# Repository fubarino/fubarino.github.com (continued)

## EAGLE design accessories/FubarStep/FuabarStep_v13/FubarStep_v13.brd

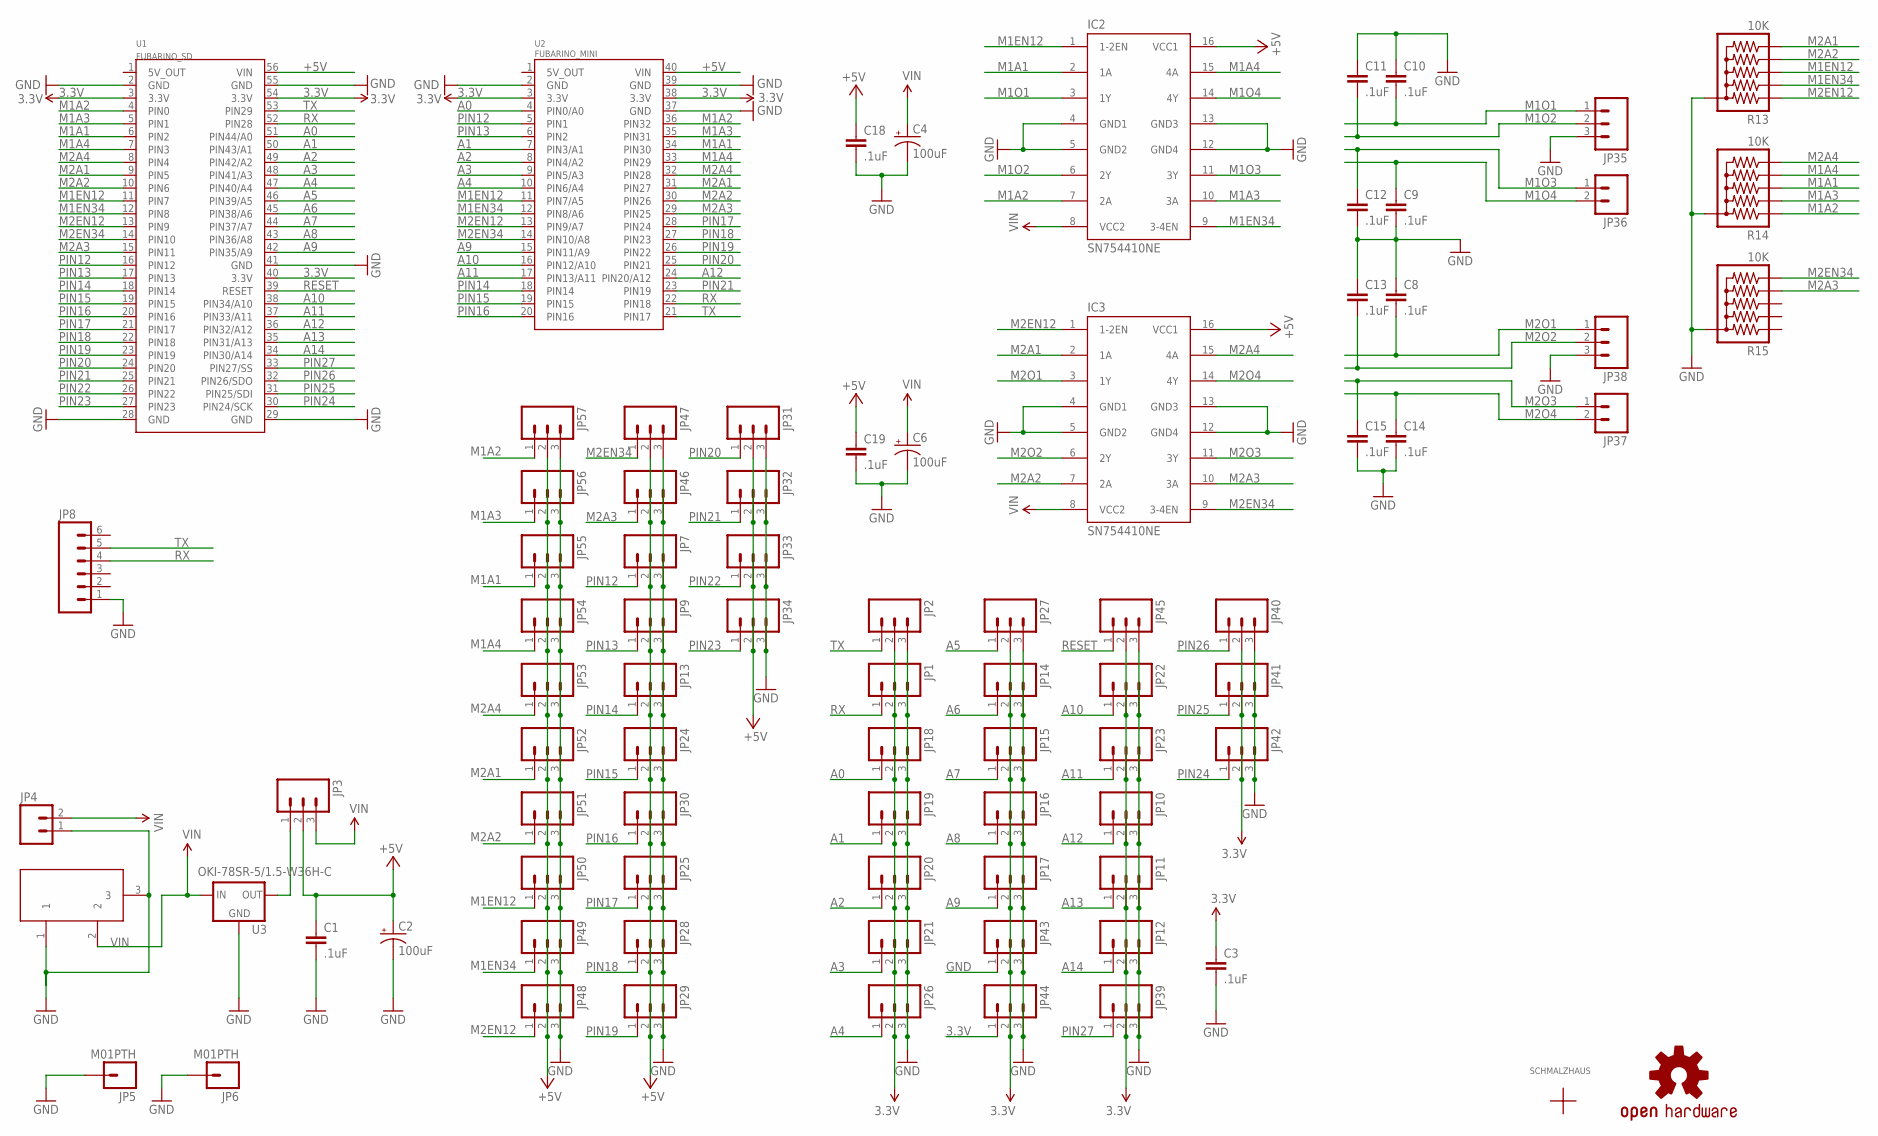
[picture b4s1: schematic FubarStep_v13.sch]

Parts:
C1, C3, C8, C9, C10, C11, C12, C13, C14, C15, C18, C19: .1uF; CAP-PTH-SMALL
C2, C4, C6: 100uF; CPOL-RADIAL-100UF
IC2, IC3: SN754410NE; DIL16
JP1, JP2, JP3, JP7, JP9, JP10, JP11, JP12, JP13, JP14, JP15, JP16, JP17, JP18, JP19, JP20, JP21, JP22, JP23, JP24, JP25, JP26, JP27, JP28, JP29, JP30, JP31, JP32, JP33, JP34, JP39, JP40, JP41, JP42, JP43, JP44, JP45, JP46, JP47, JP48, JP49, JP50, JP51, JP52, JP53, JP54, JP55, JP56, JP57: M03PTH; 1X03
JP4, JP36, JP37: M023.5MM; SCREWTERMINAL-3.5MM-2
JP5, JP6: M01PTH; 1X01
JP8: M06LOCK; 1X06_LOCK
JP35, JP38: M03SCREW; SCREWTERMINAL-3.5MM-3
LOGO1: OSHW-LOGOM; OSHW-LOGO-M
R13, R14, R15: 10K; RPACK-SIP-PTH-5
U1: FUBARINO_SD
U2: FUBARINO_MINI
U3: OKI-78SR-5/1.5-W36H-C; TO220-IGO
U$1: SCHMALZHAUSSCHMALZHAUS_SMALL; SCHMALZHAUS_SMALL
X1: DC21MMX; DC-21MM

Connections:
3.3V: C3.1, JP1.2, JP2.2, JP10.2, JP11.2, JP12.2, JP14.2, JP15.2, JP16.2, JP17.2, JP18.2, JP19.2, JP20.2, JP21.2, JP22.2, JP23.2, JP26.2, JP27.2, JP39.2, JP40.2, JP41.2, JP42.2, JP43.2, JP44.1, JP44.2, JP45.2, U1.3 (3.3V), U1.40 (3.3V), U1.54 (3.3V), U2.3 (3.3V), U2.38 (3.3V)
+5V: C1.1, C2.1 (+), C18.1, C19.1, IC2.16 (VCC1), IC3.16 (VCC1), JP3.2, JP7.2, JP9.2, JP13.2, JP24.2, JP25.2, JP28.2, JP29.2, JP30.2, JP31.2, JP32.2, JP33.2, JP34.2, JP46.2, JP47.2, JP48.2, JP49.2, JP50.2, JP51.2, JP52.2, JP53.2, JP54.2, JP55.2, JP56.2, JP57.2, U1.56 (VIN), U2.40 (VIN)
A0: JP18.1, U1.51 (PIN44/A0), U2.4 (PIN0/A0)
A1: JP19.1, U1.50 (PIN43/A1), U2.7 (PIN3/A1)
A2: JP20.1, U1.49 (PIN42/A2), U2.8 (PIN4/A2)
A3: JP21.1, U1.48 (PIN41/A3), U2.9 (PIN5/A3)
A4: JP26.1, U1.47 (PIN40/A4), U2.10 (PIN6/A4)
A5: JP27.1, U1.46 (PIN39/A5)
A6: JP14.1, U1.45 (PIN38/A6)
A7: JP15.1, U1.44 (PIN37/A7)
A8: JP16.1, U1.43 (PIN36/A8)
A9: JP17.1, U1.42 (PIN35/A9), U2.15 (PIN11/A9)
A10: JP22.1, U1.38 (PIN34/A10), U2.16 (PIN12/A10)
A11: JP23.1, U1.37 (PIN33/A11), U2.17 (PIN13/A11)
A12: JP10.1, U1.36 (PIN32/A12), U2.24 (PIN20/A12)
A13: JP11.1, U1.35 (PIN31/A13)
A14: JP12.1, U1.34 (PIN30/A14)
GND: C1.2, C2.2 (-), C3.2, C4.2 (-), C6.2 (-), C8.1, C9.2, C10.1, C11.1, C12.2, C13.1, C14.2, C15.2, C18.2, C19.2, IC2.4 (GND1), IC2.5 (GND2), IC2.12 (GND4), IC2.13 (GND3), IC3.4 (GND1), IC3.5 (GND2), IC3.12 (GND4), IC3.13 (GND3), JP1.3, JP2.3, JP4.1, JP5.1, JP6.1, JP7.3, JP8.1, JP9.3, JP10.3, JP11.3, JP12.3, JP13.3, JP14.3, JP15.3, JP16.3, JP17.3, JP18.3, JP19.3, JP20.3, JP21.3, JP22.3, JP23.3, JP24.3, JP25.3, JP26.3, JP27.3, JP28.3, JP29.3, JP30.3, JP31.3, JP32.3, JP33.3, JP34.3, JP35.3, JP38.3, JP39.3, JP40.3, JP41.3, JP42.3, JP43.1, JP43.3, JP44.3, JP45.3, JP46.3, JP47.3, JP48.3, JP49.3, JP50.3, JP51.3, JP52.3, JP53.3, JP54.3, JP55.3, JP56.3, JP57.3, R13.P$1 (1), R14.P$1 (1), R15.P$1 (1), U1.2 (GND), U1.28 (GND), U1.29 (GND), U1.41 (GND), U1.55 (GND), U2.2 (GND), U2.37 (GND), U2.39 (GND), U3.GND, X1.1, X1.3
M1A1: IC2.2 (1A), JP55.1, R14.P$4 (4), U1.6 (PIN2), U2.34 (PIN30)
M1A2: IC2.7 (2A), JP57.1, R14.P$2 (2), U1.4 (PIN0), U2.36 (PIN32)
M1A3: IC2.10 (3A), JP56.1, R14.P$3 (3), U1.5 (PIN1), U2.35 (PIN31)
M1A4: IC2.15 (4A), JP54.1, R14.P$5 (5), U1.7 (PIN3), U2.33 (PIN29)
M1EN12: IC2.1 (1-2EN), JP50.1, R13.P$4 (4), U1.11 (PIN7), U2.11 (PIN7/A5)
M1EN34: IC2.9 (3-4EN), JP49.1, R13.P$3 (3), U1.12 (PIN8), U2.12 (PIN8/A6)
M1O1: C10.2, IC2.3 (1Y), JP35.1
M1O2: C11.2, IC2.6 (2Y), JP35.2
M1O3: C12.1, IC2.11 (3Y), JP36.1
M1O4: C9.1, IC2.14 (4Y), JP36.2
M2A1: IC3.2 (1A), JP52.1, R13.P$6 (6), U1.9 (PIN5), U2.31 (PIN27)
M2A2: IC3.7 (2A), JP51.1, R13.P$5 (5), U1.10 (PIN6), U2.30 (PIN26)
M2A3: IC3.10 (3A), JP46.1, R15.P$5 (5), U1.15 (PIN11), U2.29 (PIN25)
M2A4: IC3.15 (4A), JP53.1, R14.P$6 (6), U1.8 (PIN4), U2.32 (PIN28)
M2EN12: IC3.1 (1-2EN), JP48.1, R13.P$2 (2), U1.13 (PIN9), U2.13 (PIN9/A7)
M2EN34: IC3.9 (3-4EN), JP47.1, R15.P$6 (6), U1.14 (PIN10), U2.14 (PIN10/A8)
M2O1: C8.2, IC3.3 (1Y), JP38.1
M2O2: C13.2, IC3.6 (2Y), JP38.2
M2O3: C15.1, IC3.11 (3Y), JP37.1
M2O4: C14.1, IC3.14 (4Y), JP37.2
unnamed: JP3.1, U3.OUT
PIN12: JP7.1, U1.16 (PIN12), U2.5 (PIN1)
PIN13: JP9.1, U1.17 (PIN13), U2.6 (PIN2)
PIN14: JP13.1, U1.18 (PIN14), U2.18 (PIN14)
PIN15: JP24.1, U1.19 (PIN15), U2.19 (PIN15)
PIN16: JP30.1, U1.20 (PIN16), U2.20 (PIN16)
PIN17: JP25.1, U1.21 (PIN17), U2.28 (PIN24)
PIN18: JP28.1, U1.22 (PIN18), U2.27 (PIN23)
PIN19: JP29.1, U1.23 (PIN19), U2.26 (PIN22)
PIN20: JP31.1, U1.24 (PIN20), U2.25 (PIN21)
PIN21: JP32.1, U1.25 (PIN21), U2.23 (PIN19)
PIN22: JP33.1, U1.26 (PIN22)
PIN23: JP34.1, U1.27 (PIN23)
PIN24: JP42.1, U1.30 (PIN24/SCK)
PIN25: JP41.1, U1.31 (PIN25/SDI)
PIN26: JP40.1, U1.32 (PIN26/SDO)
PIN27: JP39.1, U1.33 (PIN27/SS)
RESET: JP45.1, U1.39 (RESET)
RX: JP1.1, JP8.4, U1.52 (PIN28), U2.22 (PIN18)
TX: JP2.1, JP8.5, U1.53 (PIN29), U2.21 (PIN17)
VIN: C4.1 (+), C6.1 (+), IC2.8 (VCC2), IC3.8 (VCC2), JP3.3, JP4.2, U3.IN, X1.2

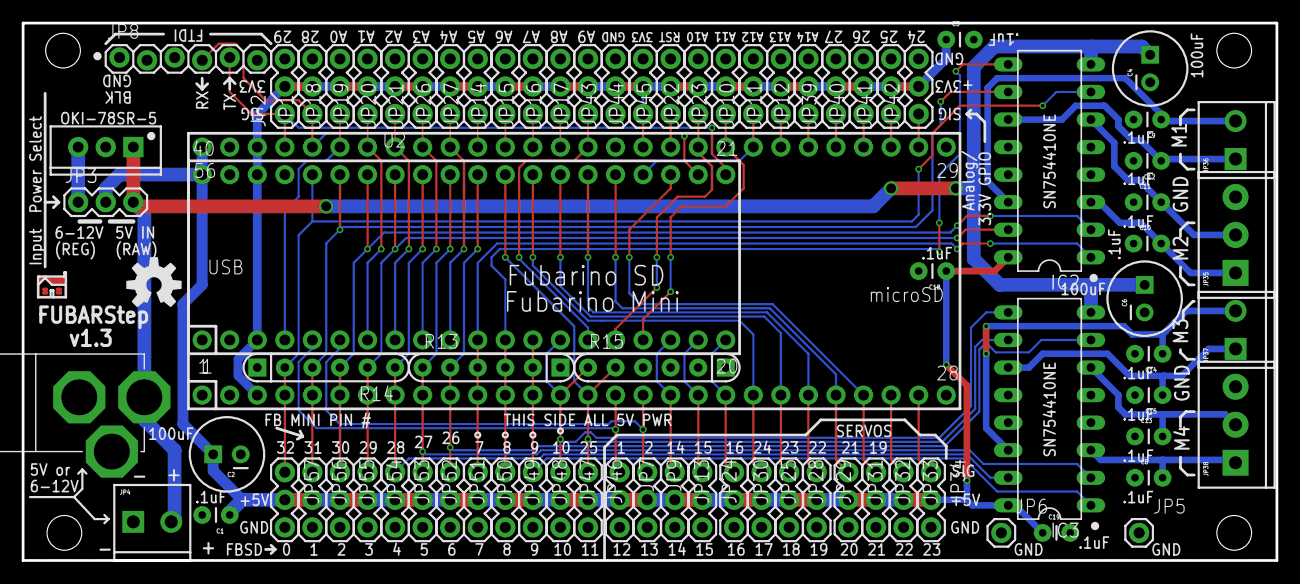
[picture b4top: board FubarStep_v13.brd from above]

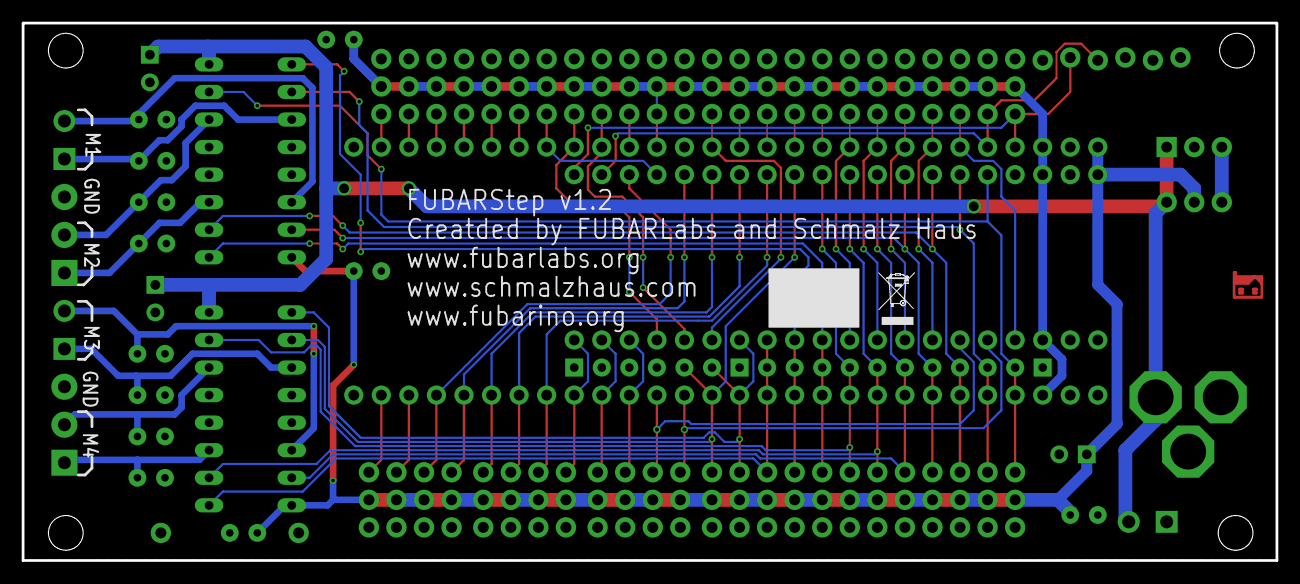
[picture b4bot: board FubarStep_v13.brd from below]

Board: 2 copper layers, 115.6 x 49.5 mm, 85 parts (2 on the bottom side), 59 nets.

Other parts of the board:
U$2: ROHS_GARBAGE_5MM
U$3: CE_5MM

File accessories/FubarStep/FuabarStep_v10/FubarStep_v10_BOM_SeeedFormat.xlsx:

Electronic Engineering BOM List
Product Name： FubarStep
Version：V1.0
Issue Date：03/13/2013
Item No. (序号) | Reference Des (上件位置) | Qty (用量) | Catalog (分类） | Part_Description (规格描述) | Part_Value （元件值） | Part_Package （元件封装） | Manufacturers Name (使用厂牌名称) | Manufacturers Part No. (使用厂牌型号) | Distributors Name （供应商名称） | Distributors Part No. (供貨商型号) | Unit Price （单价） | Price Break To Use （价格分段的购买量） | Notes/Remark （备注）
Example（填写范例）
1 | U1 | 2 | Connector | 28 pin female .100" header for Fubarino SD footprint |  |  |  |  |  |  |  |  | 0
2 | U2 | 2 | Connector | 20 pin female .100" header for Fubarino Mini footprint |  |  |  |  |  |  |  |  | 0
3 | JP7,JP9,JP13,JP24,JP30,JP25,JP28,JP29,JP31,JP32,JP33, | 3 | Connector | 12 pin male .100" header for servo connections |  |  |  |  |  |  |  |  | 0
4 | JP18,JP19,JP20,Jp21,JP26,JP27,JP14,JP15,JP16,JP17,Jp22,JP23,JP10,JP11,JP12 | 3 | Connector | 15 pin male .100" header for analog connections |  |  |  |  |  |  |  |  | 0
5 | C3,C11,C10,C12,C9,C13,C8,C15,C14,C18,C19,C1 | 12 | Capacitor | .1uF through hole ceramic capactor |  |  | Murata | RPER71H104K2P1A03B | Arrow | RPER71H104K2P1A03B | 4.8500000000000001E-2 |  | 0.58200000000000007
6 | C5,C2,C17,C16 | 4 | Capacitor | 100uF >35V electrolytic through hole capacitor |  |  | Nichicon | UVR1H101MPD | Arrow | UVR1H101MPD | 4.2599999999999999E-2 |  | 0.1704
7 | IC2,IC3 | 2 | IC | SN754410NE H-Bridge in 16 PDIP |  |  | Texas Instruments | SN754410NE | Arrow | SN754410NE | 0.88990000000000002 |  | 1.7798
8 | SOC1,SOC2 | 2 | Connector | 16 PDIP socket for IC2, IC3 |  |  |  |  |  |  |  |  | 0
9 | JP1, JP2 | 2 | Connector | 4-pin 3.5mm screw terminal |  |  |  |  |  |  |  |  | 0
10 | JP8 | 1 | Connector | 6-pin right angle .100 male header |  |  |  |  |  |  |  |  | 0
11 | JP3 | 1 | Connector | 3-pin male .100 header for power select |  |  |  |  |  |  |  |  | 0
12 | JP4 | 1 | Connector | 2-pin 3.5mm screw terminal |  |  |  |  |  |  |  |  | 0
13 | X1 | 1 | Connector | barrel jack power input |  |  |  |  |  |  |  |  | 0
14 | U3 | 1 | IC | 5V switching regulator |  |  | Murata Power Solutions | OKI-78SR-5/1.5-W36H-C | DigiKey | 811-2196-5-ND | 4.3 |  | 4.3
15 | JP3_JUMP | 1 | Connector | .100 2-pin shorting jumper |  |  |  |  |  |  |  |  | 0
16 | PCB | 1 | OTHER | FubarStep v1.0 PCB |  |  | SeeedStudio |  |  |  | 3.4 |  | 3.4
 |  |  |  |  |  |  |  |  |  |  |  |  | 0
 |  |  |  |  |  |  |  |  |  |  |  | Total | 10.232200000000001
1. Recommended Distributor: Digi-Key, Mouser, Avnet Express, Farnell.
2. Catalog: Capacitor,Resister,Diode,Connector,Transistor,IC,PROTECTOR CATEGORY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
3. Required Fields: Item No, Reference Des, Qty, Catalog, Part_Value, Part Pack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
Optional Fields: Part_Description, Manufacturers Name, Manufacturers Part No, D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

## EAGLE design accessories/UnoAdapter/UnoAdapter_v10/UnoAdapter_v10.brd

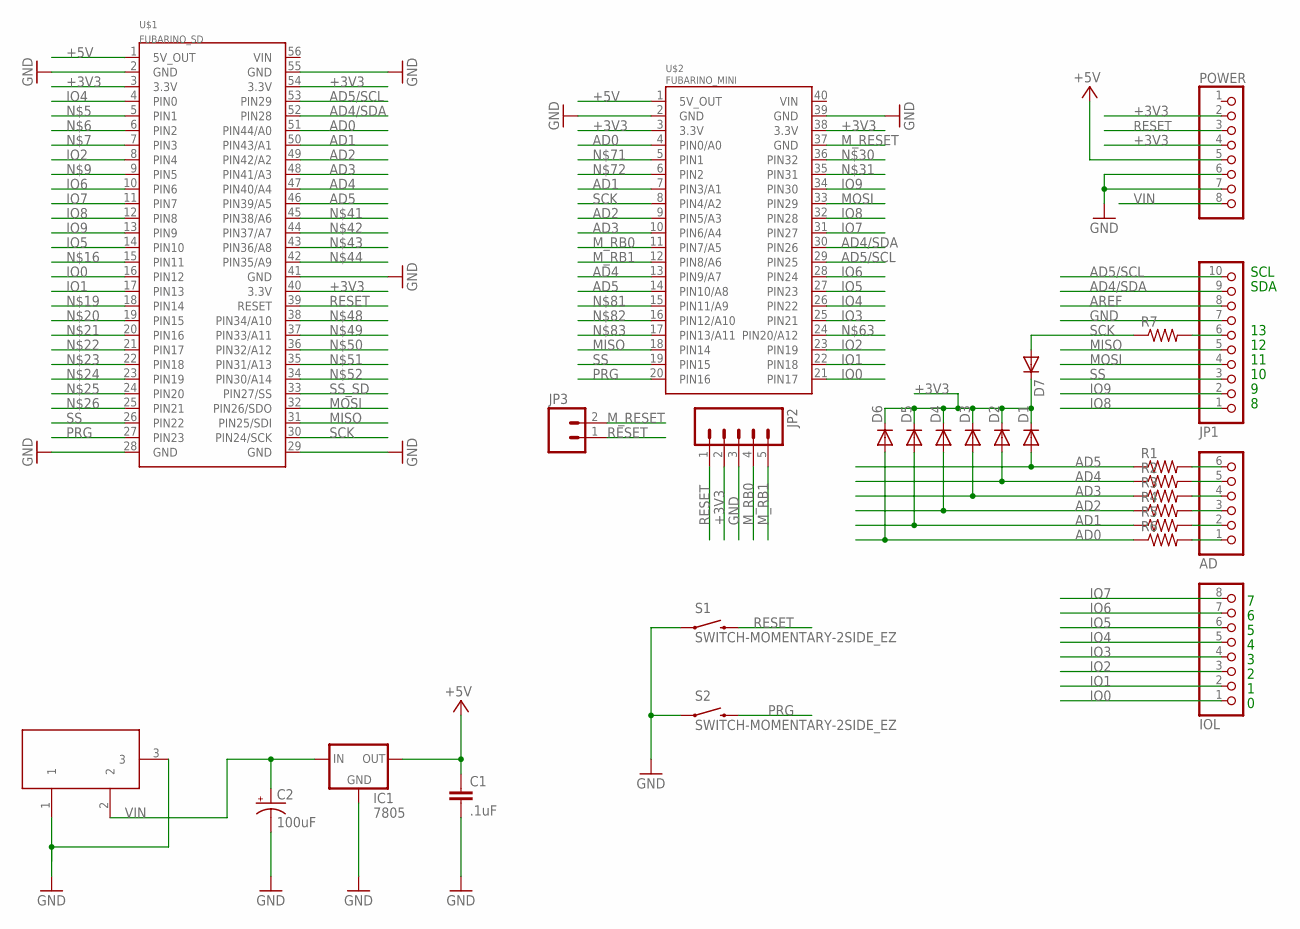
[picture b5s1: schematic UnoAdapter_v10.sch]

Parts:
AD: PINHD-1X6; 1X06
C1: .1uF; CAP-PTH-SMALL
C2: 100uF; CPOL-RADIAL-100UF-25V
D1, D2, D3, D4, D5, D6, D7: DIODE1N4148; DIODE-1N4148
IC1: 7805; 78XXL
IOL: PINHD-1X8; 1X08
JP1: PINHD-1X10; 1X10
JP2: M05PTH; 1X05
JP3: M02PTH; 1X02
POWER: PINHD-1X8; 1X08
R1, R2, R3, R4, R5, R6, R7: RESISTORAXIAL-0.3; AXIAL-0.3
S1, S2: SWITCH-MOMENTARY-2SIDE_EZ; TACTILE-PTH-SIDEEZ
U$1: FUBARINO_SD
U$2: FUBARINO_MINI
X1: DC21MMX; DC-21MM

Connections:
$12: AD.6, R1.P$2 (2)
$13: AD.5, R2.P$2 (2)
$14: AD.4, R3.P$2 (2)
$15: AD.3, R4.P$2 (2)
$16: AD.2, R5.P$2 (2)
$17: AD.1, R6.P$2 (2)
$123: JP1.6, R7.P$2 (2)
+3V3: D1.C, D2.C, D3.C, D4.C, D5.C, D6.C, D7.C, JP2.2, POWER.2, POWER.4, U$1.3 (3.3V), U$1.40 (3.3V), U$1.54 (3.3V), U$2.3 (3.3V), U$2.38 (3.3V)
+5V: C1.1, IC1.OUT, POWER.5, U$1.1 (5V_OUT), U$2.1 (5V_OUT)
AD0: D6.A, R6.P$1 (1), U$1.51 (PIN44/A0), U$2.4 (PIN0/A0)
AD1: D5.A, R5.P$1 (1), U$1.50 (PIN43/A1), U$2.7 (PIN3/A1)
AD2: D4.A, R4.P$1 (1), U$1.49 (PIN42/A2), U$2.9 (PIN5/A3)
AD3: D3.A, R3.P$1 (1), U$1.48 (PIN41/A3), U$2.10 (PIN6/A4)
AD4: D2.A, R2.P$1 (1), U$1.47 (PIN40/A4), U$2.13 (PIN9/A7)
AD4/SDA: JP1.9, U$1.52 (PIN28), U$2.30 (PIN26)
AD5: D1.A, R1.P$1 (1), U$1.46 (PIN39/A5), U$2.14 (PIN10/A8)
AD5/SCL: JP1.10, U$1.53 (PIN29), U$2.29 (PIN25)
AREF: JP1.8
GND: C1.2, C2.2 (-), IC1.GND, JP1.7, JP2.3, POWER.6, POWER.7, S1.1, S2.1, U$1.2 (GND), U$1.28 (GND), U$1.29 (GND), U$1.41 (GND), U$1.55 (GND), U$2.2 (GND), U$2.39 (GND), X1.1, X1.3
IO0: IOL.1, U$1.16 (PIN12), U$2.21 (PIN17)
IO1: IOL.2, U$1.17 (PIN13), U$2.22 (PIN18)
IO2: IOL.3, U$1.8 (PIN4), U$2.23 (PIN19)
IO3: IOL.4, U$2.25 (PIN21)
IO4: IOL.5, U$1.4 (PIN0), U$2.26 (PIN22)
IO5: IOL.6, U$1.14 (PIN10), U$2.27 (PIN23)
IO6: IOL.7, U$1.10 (PIN6), U$2.28 (PIN24)
IO7: IOL.8, U$1.11 (PIN7), U$2.31 (PIN27)
IO8: JP1.1, U$1.12 (PIN8), U$2.32 (PIN28)
IO9: JP1.2, U$1.13 (PIN9), U$2.34 (PIN30)
MISO: JP1.5, U$1.31 (PIN25/SDI), U$2.18 (PIN14)
MOSI: JP1.4, U$1.32 (PIN26/SDO), U$2.33 (PIN29)
M_RB0: JP2.4, U$2.11 (PIN7/A5)
M_RB1: JP2.5, U$2.12 (PIN8/A6)
M_RESET: JP3.2, U$2.37 (GND)
PRG: S2.2, U$1.27 (PIN23), U$2.20 (PIN16)
RESET: JP2.1, JP3.1, POWER.3, S1.2, U$1.39 (RESET)
SCK: D7.A, R7.P$1 (1), U$1.30 (PIN24/SCK), U$2.8 (PIN4/A2)
SS: JP1.3, U$1.26 (PIN22), U$2.19 (PIN15)
SS_SD: U$1.33 (PIN27/SS)
VIN: C2.1 (+), IC1.IN, POWER.8, X1.2

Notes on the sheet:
SCL
SDA

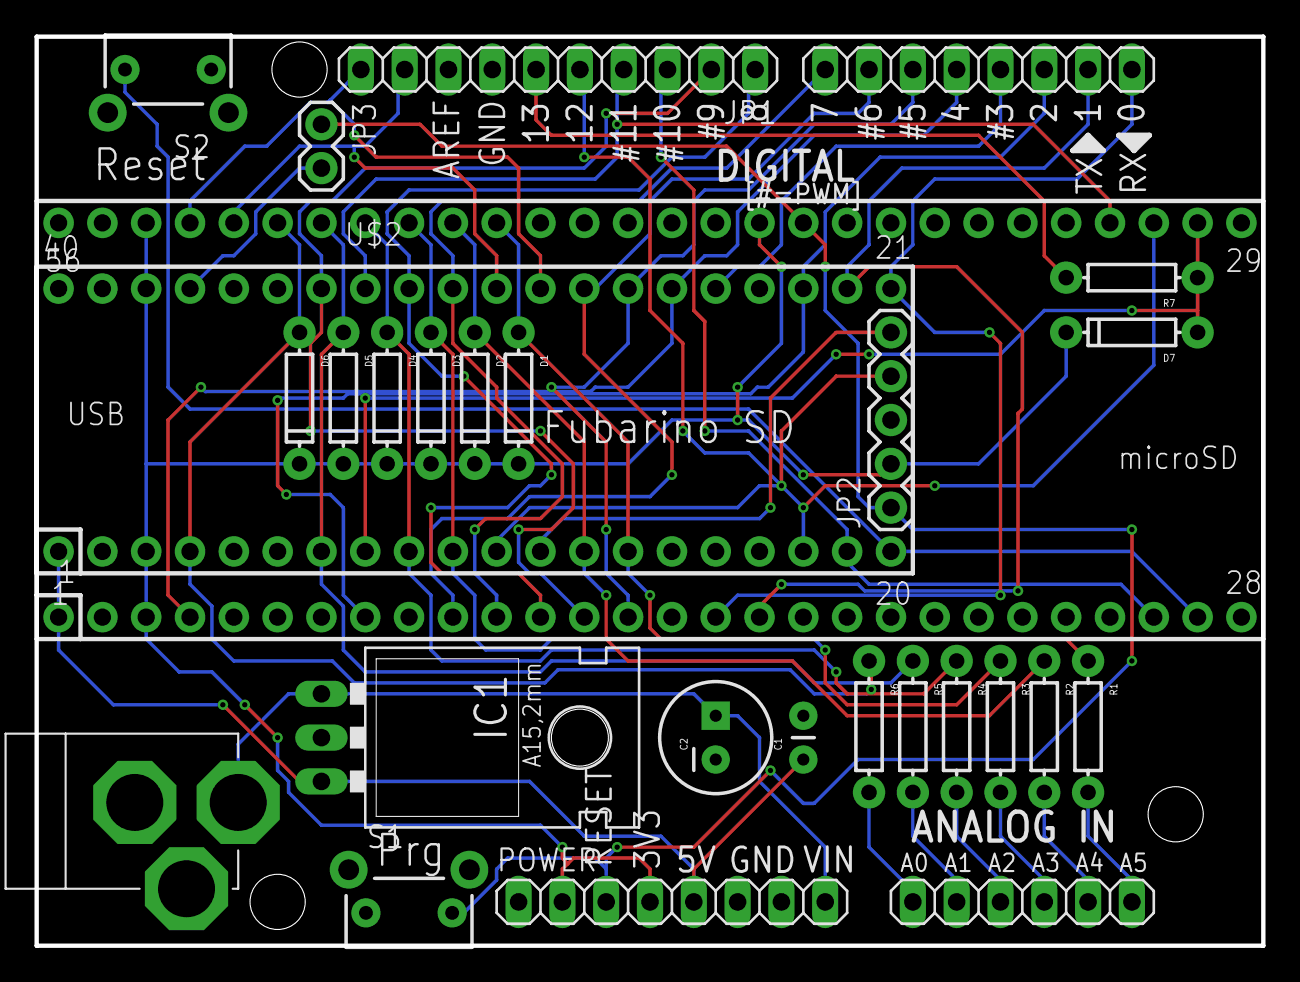
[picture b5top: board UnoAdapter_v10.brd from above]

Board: 2 copper layers, 71.1 x 52.7 mm, 28 parts (0 on the bottom side), 38 nets.

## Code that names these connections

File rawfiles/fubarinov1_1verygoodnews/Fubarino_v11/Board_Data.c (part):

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*/
//#if defined(_NOT_USED_)
const uint8_t digital_pin_to_analog_PGM[] = {
	NOT_ANALOG_PIN,	//   0  RD8
	NOT_ANALOG_PIN,	//   1  RD9
	NOT_ANALOG_PIN,	//   2  RD10
	NOT_ANALOG_PIN,	//   3  RD11
	NOT_ANALOG_PIN,	//   4  RD0
	NOT_ANALOG_PIN,	//   5  RC13
	NOT_ANALOG_PIN,	//   6  RC14
	NOT_ANALOG_PIN,	//   7  RD1
	NOT_ANALOG_PIN,	//   8  RD2
	NOT_ANALOG_PIN,	//   9  RD3
	NOT_ANALOG_PIN,	//  10  RD4
	NOT_ANALOG_PIN,	//  11  RD5
	NOT_ANALOG_PIN,	//  12  RD6
	NOT_ANALOG_PIN,	//  13  RD7
	NOT_ANALOG_PIN,	//  14  RF0
	NOT_ANALOG_PIN,	//  15  RF1
	NOT_ANALOG_PIN,	//  16  RE0
	NOT_ANALOG_PIN,	//  17  RE1
	NOT_ANALOG_PIN,	//  18  RE2
	NOT_ANALOG_PIN,	//  19  RE3
	NOT_ANALOG_PIN,	//  20  RE4
	NOT_ANALOG_PIN,	//  21  RE5
	NOT_ANALOG_PIN,	//  22  RE6
	NOT_ANALOG_PIN,	//  23  RE7
	NOT_ANALOG_PIN,	//  24  RG6
	NOT_ANALOG_PIN,	//  25  RG7
	NOT_ANALOG_PIN,	//  26  RG8
	NOT_ANALOG_PIN,	//  27  RG9
	NOT_ANALOG_PIN,	//  28  RF4
	NOT_ANALOG_PIN, //  29  RF5
	_BOARD_AN4, 	//  30  RB4   A14
	_BOARD_AN3, 	//  31  RB3   A13
	_BOARD_AN2,	    //  32  RB2   A12
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
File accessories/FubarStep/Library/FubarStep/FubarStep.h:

#ifndef FubarStep_h
#define FubarStep_h
/*

	FubarStep Library
	This library enables all the default defines for the FubarStep Motor, Stepper, Servo shield.




*/

#include <SoftPWMServo.h> 
#include <AccelStepper.h>

extern AccelStepper stepper1; 
extern AccelStepper stepper2; 


// For Fubarino SD
#if defined(_BOARD_FUBARINO_SD_)
#define M1EN12  7
#define M1EN34  8

#define M1A1    2
#define M1A2    0
#define M1A3    1
#define M1A4    3

#define M2EN12  9
#define M2EN34  10

#define M2A1    5
#define M2A2    6
#define M2A3    11
#define M2A4    4
// SD has all 12 servos hooked up
#define SRV1    12
#define SRV2    13
#define SRV3    14
#define SRV4    15
#define SRV5    16
#define SRV6    17
#define SRV7    18
#define SRV8    19
#define SRV9    20
#define SRV10   21
#define SRV11   22
#define SRV12   23
#endif

// For Fubarino Mini
#if defined(_BOARD_FUBARINO_MINI_)
#define M1EN12  7
#define M1EN34  8

#define M1A1    30
#define M1A2    32
#define M1A3    31
#define M1A4    29

#define M2EN12  9
#define M2EN34  10

#define M2A1    27
#define M2A2    26
#define M2A3    25
#define M2A4    28
// Mini only has 10 servos hooked up
#define SRV1    1   // "Pin12"     // NOTE: this is the same as the Fubar Mini's green LED
#define SRV2    2   // "Pin13"
// Note pin 14 and pin 15 are not available if using a crystal (default)
#define SRV3    14  // "Pin 14"
#define SRV4    15  // "Pin 15"
#define SRV5    16  // "Pin 16"
#define SRV6    24  // "Pin 17"
#define SRV7    23  // "Pin 18"
#define SRV8    22  // "Pin 19"
#define SRV9    21  // "Pin 20"
#define SRV10   19  // "Pin 21"
#endif

void FubarStepInit();
void motor1output(int state);
void motor2output(int state);
void forwardstep1();
void backwardstep1();
void forwardstep2();
void backwardstep2();

extern AccelStepper stepper1; 
extern AccelStepper stepper2; 


#endif

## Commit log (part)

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2012-05-01 Fubarino support files for MPIDE.
2012-08-19 Files for website.
2012-08-19 added CNAME redirection
2012-08-19 These files are now part of the MPIDE distribution rc4 and onward.
2012-08-19 Raw dump of files. Need to organize for documentation.
2012-08-19 Updated the readme.
2012-08-19 updated the readme file.
2012-08-19 Update the description with initial text.
2012-08-19 fixed error in CNAME.
2012-08-20 Updates for Fubarino images and pages. More work to be done.
2012-08-20 More boards added. Mech Fuwarefare.
2012-08-20 Update url in CNAME to org so it matches silk screen.
2012-08-31 Version v1.4 Fubarino SD board files, and manufacturing HEX and test files committed.
2012-09-03 Starting Reference Manual for Fubarino SD
2012-09-06 added images for the fubarinosd.
2012-09-06 Added breadcrumb.
2012-09-06 add images
2012-09-07 added logo image jpg
2012-09-07 updated site from cloud9ide.
2012-09-07 added more files.
2012-09-07 almost there.
2012-09-07 closer to good enough.
2012-09-07 Cropped some images.
2012-09-07 image clean up.
2012-09-14 Updated the seeed studion link
2012-09-14 Update a typo
2012-09-14 Updated feature list
2012-09-28 Updated Fubarino SD diagram to be vertical, with pin numbers for LED and PRG buttons.
2012-10-14 updated with links to wiki, and mpide.
2012-10-14 more wiki link added.
2012-10-24 Updated pin diagram with some nice colors. Updated Reference Manual with bare minimum information.
2012-10-25 Updated FubarinoSD reference manual with pin table, created PDF of manual as well.
2012-10-26 Updated ref manual with Rick's changes.
2013-01-01 Fixed reference to UART in diagrams for pins 8,9
2013-01-11 Updated silk screen with chipKIT, RX (pin 8) and TX (pin 9) Bumped rev to 1.5
2013-01-12 Added Rick's QR code to top silk layer. Still v1.5
2013-01-13 Starting Uno Adapter board
2013-01-13 More work on Uno Adapter
2013-01-13 Added Fubarino Mini to board.
2013-01-23 Moved Fubarinos around, added regulator.
2013-01-29 Checking in FubarinoMini v1.0 through v1.4, all files including gerbers.
2013-02-19 Updated SVG diagram as per Jacob's suggestion (A8/A7 mistake) Updated reference manual with updated diagram. Updated schematic to 1.4.1, with 5V net renamed to Vout as per Jaocb's suggestion.
2013-02-20 Updated to the how to program the Fubarino SD.
2013-02-20 Fubarino SD programming video update.
2013-02-20 Project directory and videos added.
2013-02-20 added project directory
2013-02-20 Fixed part of SD directory heading
2013-02-24 Added missing text from v1.4
2013-02-24 Start on version 1.5 for Microchip - added CE, RoSH garbage can, and chipKIT logos to bottom silk layer.
2013-02-24 Created first pass of assembly drawing, drill drawing, and BOM in Microchip format.
2013-02-27 "final" version 1.5 files, submitted to Microchip for their approval Updated USB connector footprint to Microchip's fav Hirose
2013-02-27 Added license text to schematic.
2013-02-27 Swapped USB connector for Microchip's Hirose.
2013-02-27 Updated Fubarino SD v1.5 board with CE, RoHS, chipKIT on silk, updated BOM, rendered top and bottom from gerbers.
2013-02-27 "Final" Fubarino Mini v1.5 files for Microchip. Fixed several minor documentation errors, created all new files, created IPC and PNP files.
2013-02-27 "Final" Fubarino SD v1.5 files to Microchip, including IPC and PNP.
2013-02-28 Corrected CPU in BOM for Fubatino SD to MX795.
2013-02-28 Updated Fubarino SD BOM to use IC2 as the designator for the LDO as the schematic does.
2013-02-28 Corrected CPU on Fubarino Mini v1.5 to be the VQFN package rather than the VTLA package.
2013-03-08 Starting the new stepper shield.
2013-03-10 More work.
2013-03-10 Oops. forgot to add new files
2013-03-10 Updated board a bit.
2013-03-10 Started routing. And assigned all the pins except for Mini to SD.
2013-03-10 More routing.
2013-03-11 Routing is done, but Mini connections not yet made. Top silk is almost done.
2013-03-13 Version 1.0 done - routed, schematic done (with license), just need to add BOM now.
2013-03-13 Added power mode jumper to select between 12V and 5V inputs. Added two ground pins for debugging Added 2-pin screw terminal for extra power input option.
2013-03-13 Started BOM - not quite complete yet.
2013-03-14 Got some more work done on the board - fixed power issues, added reset/prg switches, moved Fubarinos inside Uno headers.
2013-03-14 Updated BOM - each unit is $15.73
2013-03-15 Version 1.6 of Fubarino Mini - replaced GND on J2 pin 17 with RESET so that we can use external reset button with shields and such.
2013-03-19 Update to UnoAdapter - still not done yet. Added Fubarino Mini v1.6 files (brought MCLR out to side pin)
2013-03-19 Adding combined bootloader + functional test sketch HEX files for both Fubarino SD and Mini. Adding functional test sketch for Fubarino Mini.
2013-03-19 Updated BOM on v1.6 Mini to use 820 ohm current limits rather than 330s.
2013-03-21 First rough draft of schematic done, first super crappy routing done.
2013-04-02 FUBARStep v1.0 board works. Created notes.txt with build notes. Also created test sketch and demo video with that sketch.
2013-04-02 Created FUBARStep v1.1 - fixed problems found with v1.0 build
2013-04-03 Created 'Simple' Fubarino Mini tests for Microchip that doesn't want to build a test jig. Version 1.1 of test PDE and instructions.
2013-04-07 Changed example sketch so it works with Mini and SD Fubarinos. Tested on both.
2013-04-07 Added test sketch showing four DC motor forward and backward with FubarStep.
2013-04-07 Added sketch showing four DC motors ramping up and ramping down with PWM on FubarStep.
2013-04-12 update wiki links.
2013-04-12 Initial FubarStep Library files.
2013-05-01 Fixed a minor silk screen error from FubarStep v1.0 Added RoSH and CE logos to back silk
2013-05-02 Starting the Fubarino Mini docs
2013-05-04 Made board taller so that we could fit screws into the mounding holes. Added silk on all pins for better documentation. Ordered this exact board from OSHPark.
2013-05-04 Updated user ref manual for Mini
2013-05-05 Finished first draft of Fubarino Mini User Guide - updated text and diagrams.
2013-05-10 added fubarino mini v15 image.
2013-05-10 File changes, but not page changes.
2013-05-10 edited images for carousel.
2013-05-10 Boostrap 2.3.1 udpate.
2013-05-11 Oops. Found a minor mistake on the FubarStep schematic.
2013-05-11 Started FubarStep v1.2 - fixed TX/RX swap on Mini
2013-05-12 carousel updated
2013-05-12 another carousel update
2013-05-12 Site update.
2013-05-12 flipped purchase and info links.
2013-05-12 Fixed typos.
2013-05-12 added trademark info
2013-05-12 Updated both SD and Mini user guides with updated Tools->Boards->Fubarino-> references.
2013-05-12 reverted trademark changes. Trademark needs to be added, but more subtle.
2013-05-12 Fixed the main page top layout. Need to fix the containers
2013-05-15 Update Fubarino Mini buy links, and Fubarino Mini Carousel image.:
2013-05-15 fixed link typo.
2013-05-17 Working with library - cleaned things up a little, creating examples for Maker Faire.
2013-05-20 Fixed issues with links and button format on index files.
2013-05-20 Fixed links for purchase of mini.
2013-05-20 Added mailing list signup.
2013-06-10 Updated the hardware spec for version 1.5 in description.
2013-06-12 Just playing with some ideas for v1.2 board - adding headers to every pin, for a complete break out board type feel.
2013-07-24 Added bower, angular, and some ChipKit -> chipKIT conversions.
2013-07-24 Added bower, angular, and some ChipKit -> chipKIT conversions. more
2013-08-05 Testing Disqus
2013-08-12 Added PDFs of board and schematic for FubarStep v1.1
2013-10-31 New version of FubarStep - almost ready to go.
2013-11-04 Sent these boards off to Seeed for production.
2013-12-03 Getting started with next version of FubarStep board.
2013-12-25 Fixes #7 typo in file.
2014-01-08 Fixed wrong part suffix.
2014-02-01 Checking in to make sure I have all changes.
2014-02-02 Version 1.3 ready for review. Added pull down resistors to H-Bridge inputs, tweaked part placement for better assembly and silk screen for more information and readability.
2014-03-11 Created PIC32MX795F512H symbol, and updated schematic with it. Also had to re-do nets to CPU on layout because Eagle reasons.
2014-04-08 Updated Fubarino Mini documentation to make it more clear that some pins are already used and can't easily be used for GPIO.
2014-04-15 Updated Fubarino Mini doc with default hardware PWM pins (0, 4, 7, 8 and 9)
2014-05-02 Minor spelling corrections, and switching to "chipKIT Fubarino" word order for both boards (per Microchip's recommendation), and adding TM to Fubarino and chipKIT.
2014-05-10 Starting on Fubarino SDZ.
2014-05-12 More work on FBSDZ
2014-05-21 This version got sent to seed for fab - v 1.0
2014-05-21 Renamed with SDZ.
2014-06-02 Some little change in the board.
2014-07-05 Added files for PnP operation (untested)
2014-07-06 Forgot the ulp file.
2014-07-07 Got most of the PnP running. The Fubarino_SDZ_v10_Top.csv file has all the good stuff.
2014-07-09 Final PnP command file we used to build 21 Fubarino SDZ boards.
2015-01-30 Created Fritzing part for Fubarino SD.
2015-01-31 Updated Fubarino SD Fritzing part- * Added real holes for pins * Added details to microSD and USB connectors to make them more visually appealing
2015-01-31 Added Fritzing part for Fubarino Mini v1.5
2015-03-07 Updated Fubarino Mini pin diagram.
2015-03-10 Updated pin diagram for Fubarino Min with power information and 5V tolerant pins.
2015-09-13 Created version 1.5 - Switched VBUS PIC32 to be connected to VBUS net rather than 5V.
2015-09-14 Fixed typos and added Fubarino Mini purchase link.
2015-09-14 Fixed minor typo.
2015-10-04 Working on FBMiniProto
2016-03-26 Updated SVG pin diagram with correct analog pin names, created EPS version, updated User Reference Manual with updated diagram EPS file. Also updated pin table in Ref Manual with actual analog pin na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
2016-03-26 Removed whitespace around png FB Mini pin diagram.
2016-03-26 Added PDF version of updated FBmini pin diagram.
2016-08-19 Issue #19 closed by updating Fubarino Mini diagram.
2017-03-04 Updating Fubarino Mini pin diagram to have correct SPI1 pins
2017-03-04 Updated Fubarino Mini pin diagram and Reference Manual to use correct pins for SPI (SPI1) port, also added sections in ref manual giving table of SPI1 and SPI2 pins.
2017-07-10 Added production idea from Rick.
2017-07-14 Checking in extra files - mainly for FubarStep v1.3
2017-08-04 Checking in board pdf.
2017-08-17 Added pdfs and pngs of FubarStep board v1.3 board and schematic
2017-08-28 Most recent changes to the pinout digram for the FubarStep.
2018-03-03 Fixed error in A7 (was A8) in SVG)
2018-05-03 Updated design to final v1.7 - see Notes.txt for change list
2018-05-03 Updated notes and schematic to reflect new CPU (MX270)
2018-05-03 Minor schematic tweak for MCLR pin label.
2018-05-03 Changed LDO to one that has 15V VIn max. Still need to updated caps on either side to be bigger.
2018-08-18 Updated change log with complete list of v1.7 changes to be done.
2018-08-18 v1.7 updates.
2018-08-19 Version 2.0, first draft, done and sent to PCB fab. Changed switches, crystal, USB connector, rerouted most of board. Still need to rename folder to 2.0
2018-08-25 Minor silk screen adjustments for readability, and moving a couple caps around for easier assembly.
2018-08-25 Renamed FB Mini v1.7 -> v2.0
2018-08-25 Finished renaming files to v2.0 for FB Mini
2018-08-25 Updated BOM with caps that are available at this minute, and added 1K parts prices.
2018-08-29 Final gerbers and documentation for Fubarino Mini v2.0 created for Microchip.
2018-10-25 Final special files for Microchip build.
2021-02-21 Fixed error on FB Mini v1.5 PNG and PDF pin diagrams (issue #26). Also created FB Mini v2.0 SVG, PDF and PNG.
2021-02-22 Whitepsace change to test my ability to push.
2021-02-22 Update CNAME
2021-02-24 Updated FubarinoMiniUserRefManual to include both v1.5 and v2.0 designs. Added pdf, png and svn diagrams with both v1.5 and 2.0 info.
